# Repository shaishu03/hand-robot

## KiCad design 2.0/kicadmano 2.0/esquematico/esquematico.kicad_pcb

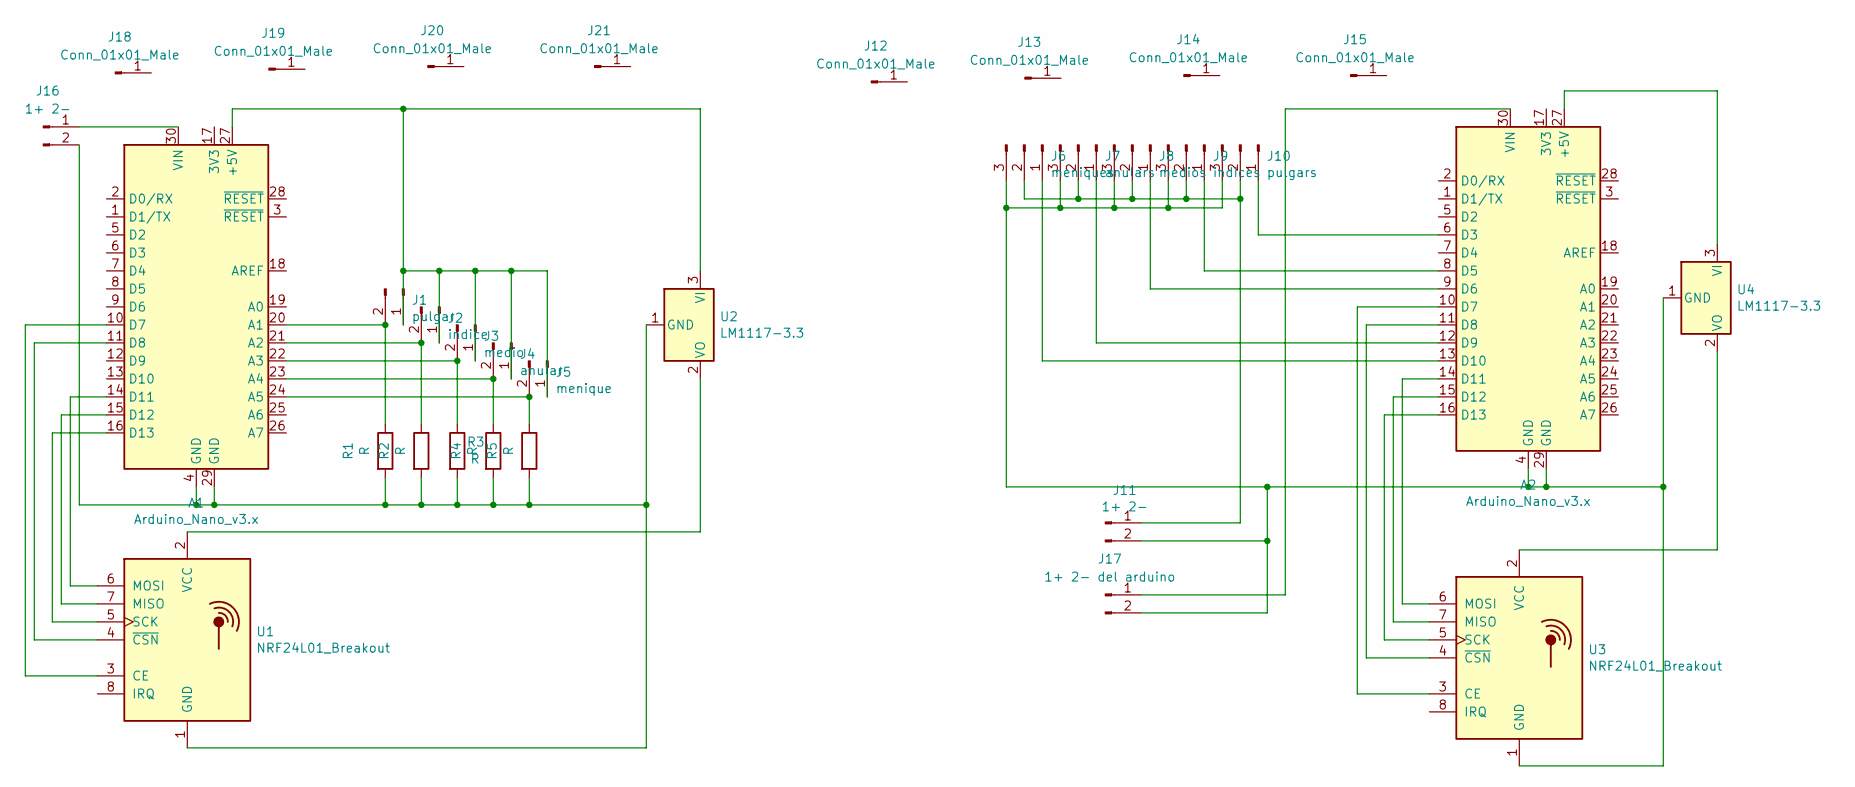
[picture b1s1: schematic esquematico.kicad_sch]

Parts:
A1, A2: Arduino_Nano_v3.x; Arduino_Nano
J1: pulgar; TO-126-2_Vertical
J2: indice; TO-126-2_Vertical
J3: medio; TO-126-2_Vertical
J4: anular; TO-126-2_Vertical
J5: menique; TO-126-2_Vertical
J6: meniques; PinHeader_1x03_P2.54mm_Vertical
J7: anulars; PinHeader_1x03_P2.54mm_Vertical
J8: medios; PinHeader_1x03_P2.54mm_Vertical
J9: indices; PinHeader_1x03_P2.54mm_Vertical
J10: pulgars; PinHeader_1x03_P2.54mm_Vertical
J11, J16: 1+ 2-; AMASS_XT30U-M_1x02_P5.0mm_Vertical
J12, J13, J14, J15, J18, J19, J20, J21: Conn_01x01_Male; Banana_Jack_1Pin
J17: 1+ 2- del arduino; AMASS_XT30U-M_1x02_P5.0mm_Vertical
R1, R2, R3, R4, R5: R; R_Axial_DIN0204_L3.6mm_D1.6mm_P7.62mm_Horizontal
U1, U3: NRF24L01_Breakout; nRF24L01_Breakout
U2, U4: LM1117-3.3; TerminalBlock_TE_282834-3_1x03_P2.54mm_Horizontal

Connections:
unnamed: A1.10 (D7), U1.3 (CE)
unnamed: A1.11 (D8), U1.4 (~CSN)
unnamed: A1.14 (D11), U1.6 (MOSI)
unnamed: A1.15 (D12), U1.7 (MISO)
unnamed: A1.16 (D13), U1.5 (SCK)
unnamed: A1.20 (A1), J1.2, R1.1
unnamed: A1.21 (A2), J2.2, R2.1
unnamed: A1.22 (A3), J3.2, R3.1
unnamed: A1.23 (A4), J4.2, R4.1
unnamed: A1.24 (A5), J5.2, R5.1
unnamed: A1.27 (+5V), J1.1, J2.1, J3.1, J4.1, J5.1, U2.3 (VI)
unnamed: A1.4 (GND), A1.29 (GND), J16.2, R1.2, R2.2, R3.2, R4.2, R5.2, U1.1 (GND), U2.1 (GND)
unnamed: A1.30 (VIN), J16.1
unnamed: A2.6 (D3), J10.1
unnamed: A2.8 (D5), J9.1
unnamed: A2.9 (D6), J8.1
unnamed: A2.10 (D7), U3.3 (CE)
unnamed: A2.11 (D8), U3.4 (~CSN)
unnamed: A2.12 (D9), J7.1
unnamed: A2.13 (D10), J6.1
unnamed: A2.14 (D11), U3.6 (MOSI)
unnamed: A2.15 (D12), U3.7 (MISO)
unnamed: A2.16 (D13), U3.5 (SCK)
unnamed: A2.27 (+5V), U4.3 (VI)
unnamed: A2.4 (GND), A2.29 (GND), J6.3, J7.3, J8.3, J9.3, J10.3, J11.2, J17.2, U3.1 (GND), U4.1 (GND)
unnamed: A2.30 (VIN), J17.1
unnamed: J6.2, J7.2, J8.2, J9.2, J10.2, J11.1
unnamed: U1.2 (VCC), U2.2 (VO)
unnamed: U3.2 (VCC), U4.2 (VO)

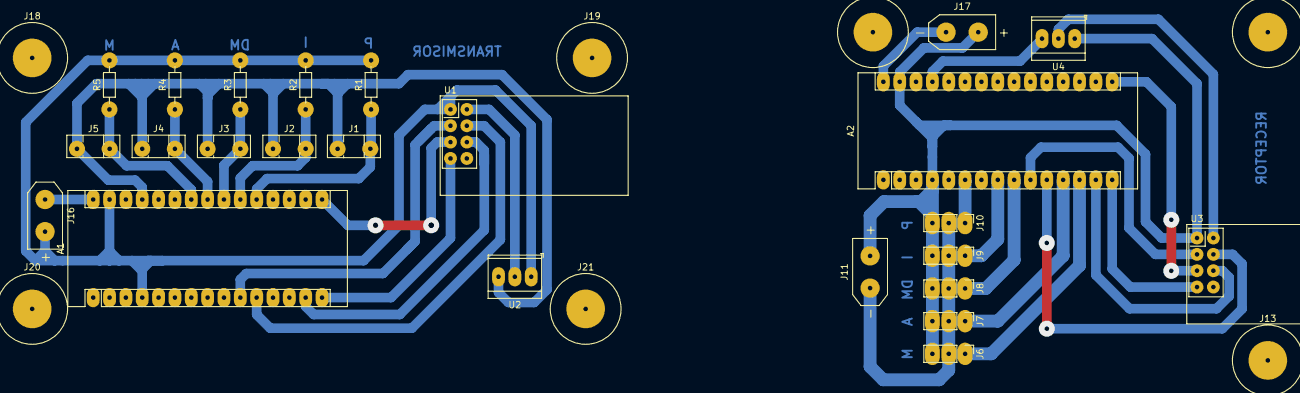
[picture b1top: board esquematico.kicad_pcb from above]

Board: 2 copper layers, 31 parts (0 on the bottom side), 29 nets.

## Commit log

2022-07-18 A function is added to the program that measures the values ​​of a person's closed hand and open hand. pcb fixed
2022-07-18 the open/closed measurement made in the setup is now as a function
